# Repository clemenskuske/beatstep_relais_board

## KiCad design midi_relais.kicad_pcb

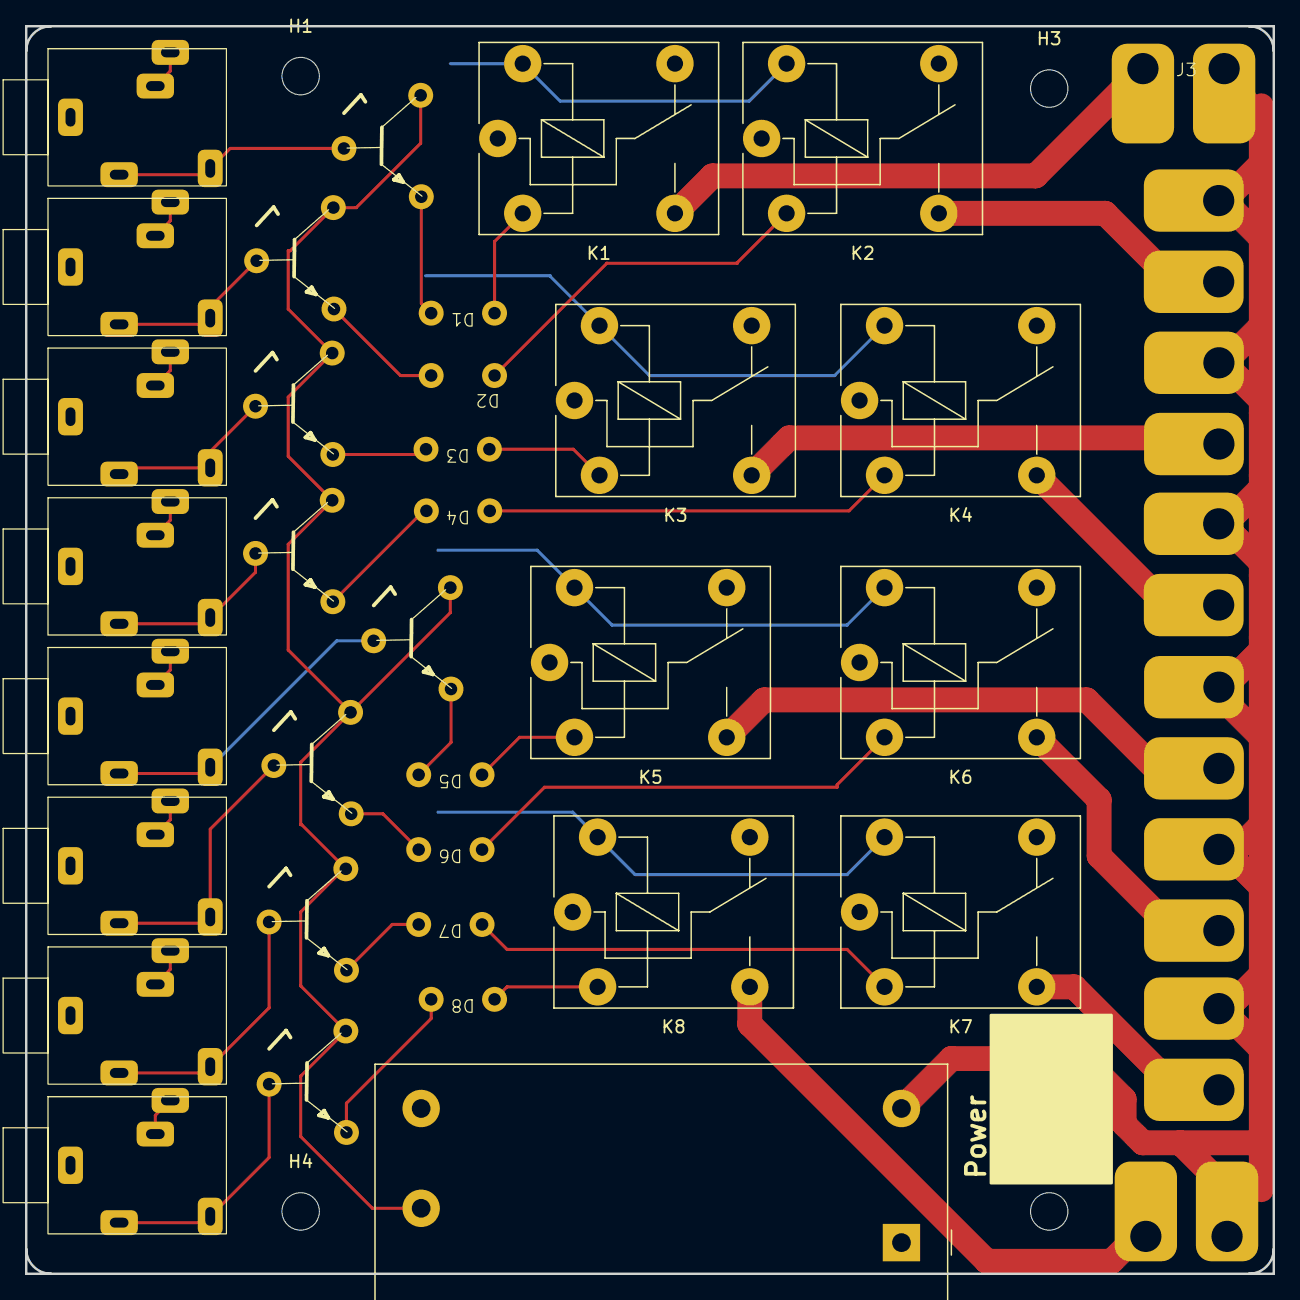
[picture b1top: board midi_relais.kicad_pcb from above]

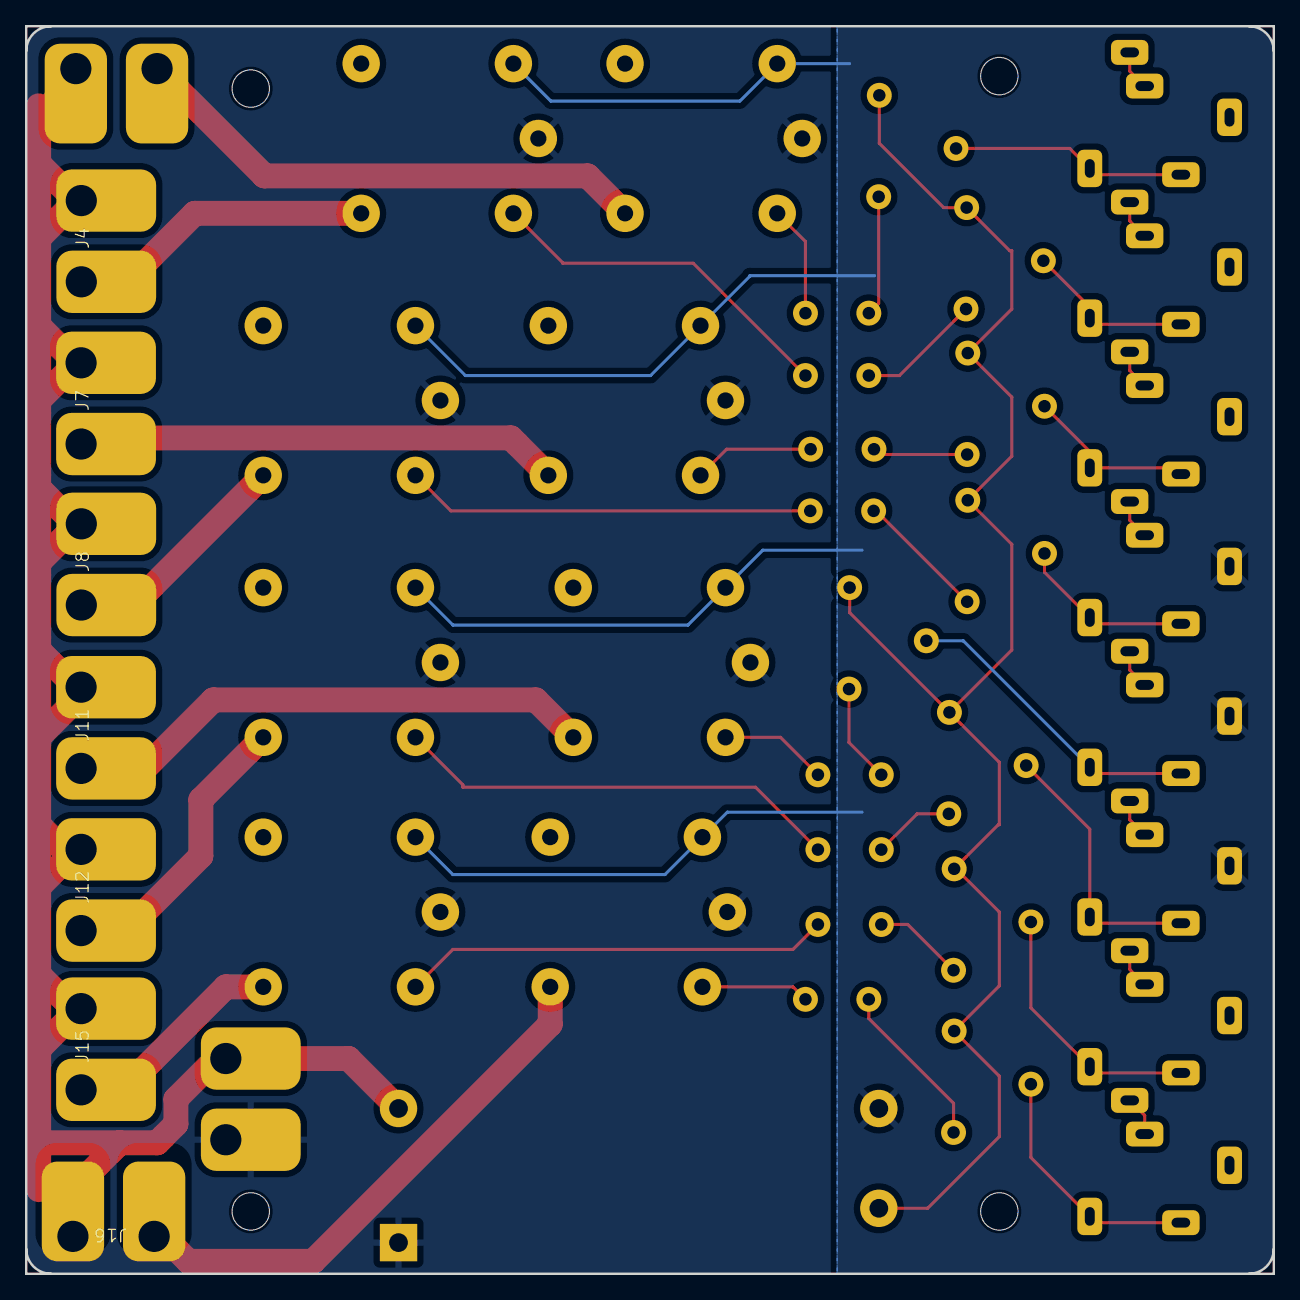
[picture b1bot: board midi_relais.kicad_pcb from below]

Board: 2 copper layers, 100.0 x 100.0 mm, 46 parts (7 on the bottom side), 36 nets.

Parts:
D1, D2, D3, D4, D5, D6, D7, D8: D; Diode
H1, H2, H3, H4: MountingHole; MountingHole_3mm
J1, J2, J5, J6, J9, J10, J13, J14: AudioJack2_Ground; klinke
J3, J4, J7, J8, J11, J12, J15, J16, J17: Conn_01x02_Pin; Connector
K1, K2, K3, K4, K5, K6, K7, K8: FINDER-36.11; Relay_SPDT_Finder_36.11
PS1: IRM-10-5; Converter_ACDC_MeanWell_IRM-05-xx_THT
Q1, Q2, Q3, Q4, Q5, Q6, Q7, Q8: 2N2219; Transistor

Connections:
+3.3V: PS1.4 (+Vo), Q1.3 (C), Q2.3 (C), Q3.3 (C), Q4.3 (C), Q5.3 (C), Q6.3 (C), Q7.3 (C), Q8.3 (C)
GND: J6.G, J9.G, J10.G, K1.A2, K2.A2, K3.A2, K4.A2, K5.A2, K6.A2, K7.A2, K8.A2, PS1.3 (-Vo)
GND2: J17.2, K1.11, K2.11, K3.11, K4.11, K5.11, K6.11, K7.11, K8.11, PS1.1 (AC/N)
unnamed: D1.2 (A), Q1.1 (E)
unnamed: D1.1 (K), K1.A1
unnamed: D2.2 (A), Q2.1 (E)
unnamed: D2.1 (K), K2.A1
unnamed: D3.2 (A), Q3.1 (E)
unnamed: D3.1 (K), K3.A1
unnamed: D4.2 (A), Q4.1 (E)
unnamed: D4.1 (K), K4.A1
unnamed: D5.2 (A), Q5.1 (E)
unnamed: D5.1 (K), K5.A1
unnamed: D6.2 (A), Q6.1 (E)
unnamed: D6.1 (K), K6.A1
unnamed: D7.2 (A), Q7.1 (E)
unnamed: D7.1 (K), K7.A1
unnamed: D8.2 (A), Q8.1 (E)
unnamed: D8.1 (K), K8.A1
unnamed: J3.1, K1.14
unnamed: J4.1, K2.14
unnamed: J7.1, K3.14
unnamed: J8.1, K4.14
unnamed: J11.1, K5.14
unnamed: J12.1, K6.14
unnamed: J15.1, K7.14
unnamed: J16.1, K8.14
unnamed: J1.S, Q1.2 (B)
unnamed: J2.S, Q2.2 (B)
unnamed: J5.S, Q3.2 (B)
unnamed: J6.S, Q4.2 (B)
unnamed: J9.S, Q5.2 (B)
unnamed: J10.S, Q6.2 (B)
unnamed: J13.S, Q7.2 (B)
unnamed: J14.S, Q8.2 (B)
VAC: J3.2, J4.2, J7.2, J8.2, J11.2, J12.2, J15.2, J16.2, J17.1, PS1.2 (AC/L)

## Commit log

2023-07-03 initial push
